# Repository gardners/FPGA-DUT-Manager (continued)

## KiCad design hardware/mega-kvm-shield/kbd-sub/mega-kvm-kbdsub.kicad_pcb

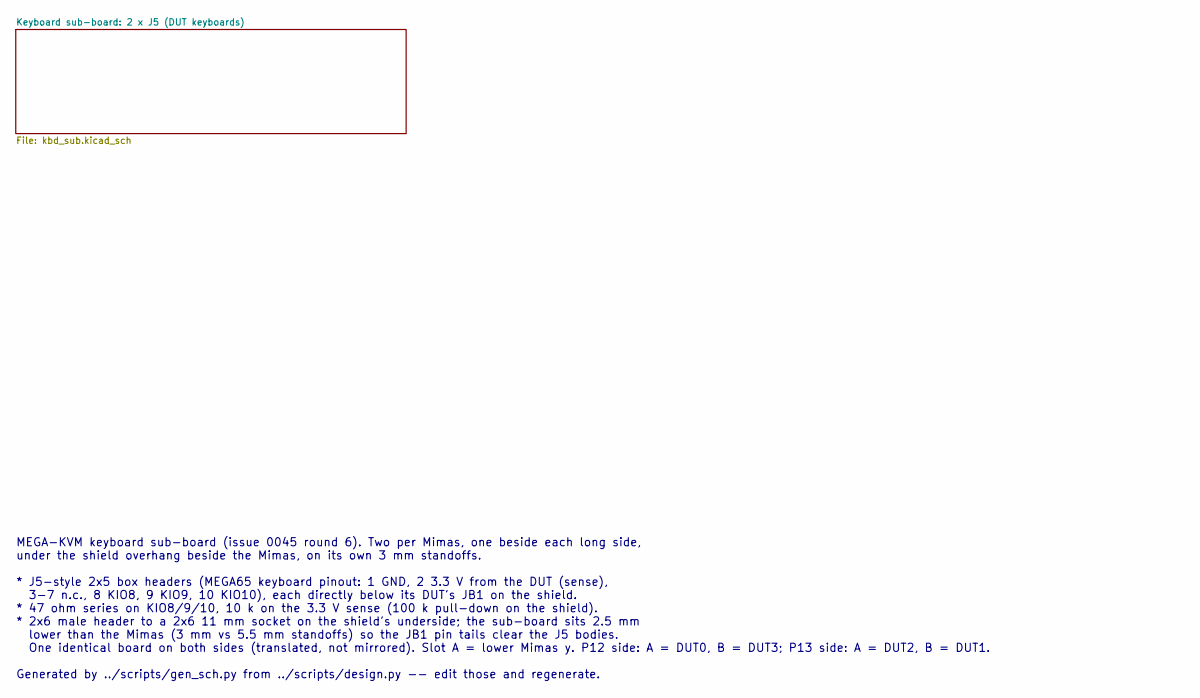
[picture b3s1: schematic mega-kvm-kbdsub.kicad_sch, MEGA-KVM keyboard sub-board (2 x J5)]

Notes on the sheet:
MEGA-KVM keyboard sub-board (issue 0045 round 6). Two per Mimas, one beside each long side, under the shield overhang beside the Mimas, on its own 3 mm standoffs. * J5-style 2x5 box headers (MEGA65 keyboard pinout: 1 GND, 2 3.3 V from the DUT (sense), 3-7 n.c., 8 KIO8, 9 KIO9, 10 KIO10), each direc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

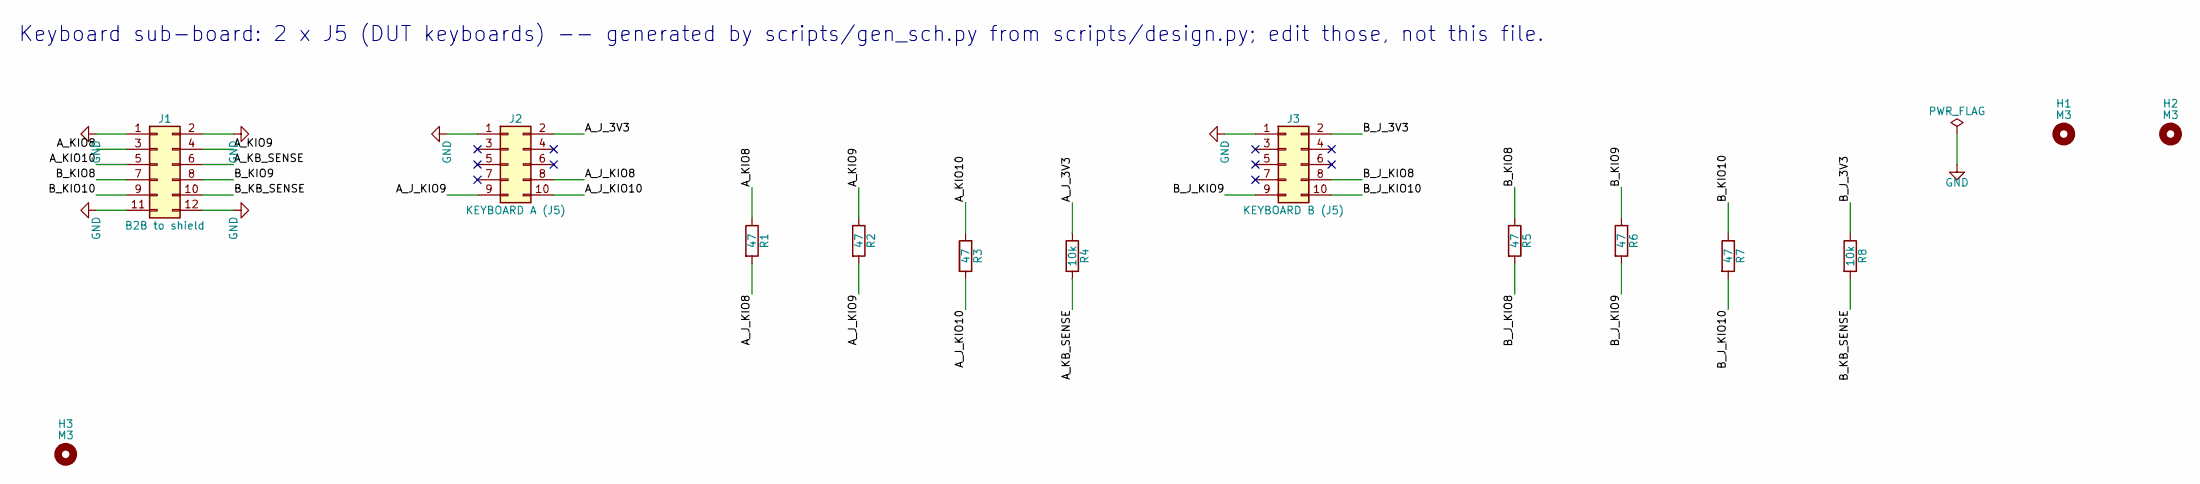
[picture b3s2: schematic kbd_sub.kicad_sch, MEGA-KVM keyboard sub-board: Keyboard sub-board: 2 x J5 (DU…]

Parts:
H1, H2, H3: M3; MountingHole_3.2mm_M3
J1: B2B to shield; PinHeader_2x06_P2.54mm_Vertical
J2: KEYBOARD A (J5); IDC-Header_2x05_P2.54mm_Horizontal
J3: KEYBOARD B (J5); IDC-Header_2x05_P2.54mm_Horizontal
R1, R2, R3, R5, R6, R7: 47; R_0402_1005Metric; LCSC C25118
R4, R8: 10k; R_0402_1005Metric; LCSC C25744

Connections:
A_J_3V3: J2.2, R4.1
A_J_KIO8: J2.8, R1.2
A_J_KIO9: J2.9, R2.2
A_J_KIO10: J2.10, R3.2
A_KB_SENSE: J1.6, R4.2
A_KIO8: J1.3, R1.1
A_KIO9: J1.4, R2.1
A_KIO10: J1.5, R3.1
B_J_3V3: J3.2, R8.1
B_J_KIO8: J3.8, R5.2
B_J_KIO9: J3.9, R6.2
B_J_KIO10: J3.10, R7.2
B_KB_SENSE: J1.10, R8.2
B_KIO8: J1.7, R5.1
B_KIO9: J1.8, R6.1
B_KIO10: J1.9, R7.1
GND: J1.1, J1.2, J1.11, J1.12, J2.1, J3.1

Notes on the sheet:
Keyboard sub-board: 2 x J5 (DUT keyboards) -- generated by scripts/gen_sch.py from scripts/design.py; edit those, not this file.

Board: 2 copper layers, 14 parts (0 on the bottom side), 17 nets, no tracks yet.

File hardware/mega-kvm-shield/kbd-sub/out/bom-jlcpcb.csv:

Comment,Designator,Footprint,LCSC Part #,MPN,Qty
B2B to shield,J1,PinHeader_2x06_P2.54mm_Vertical,TBD,,1
KEYBOARD A (J5),J2,IDC-Header_2x05_P2.54mm_Horizontal,TBD,,1
KEYBOARD B (J5),J3,IDC-Header_2x05_P2.54mm_Horizontal,TBD,,1
47,"R1,R2,R3,R5,R6,R7",R_0402_1005Metric,C25118,,6
10k,"R4,R8",R_0402_1005Metric,C25744,,2

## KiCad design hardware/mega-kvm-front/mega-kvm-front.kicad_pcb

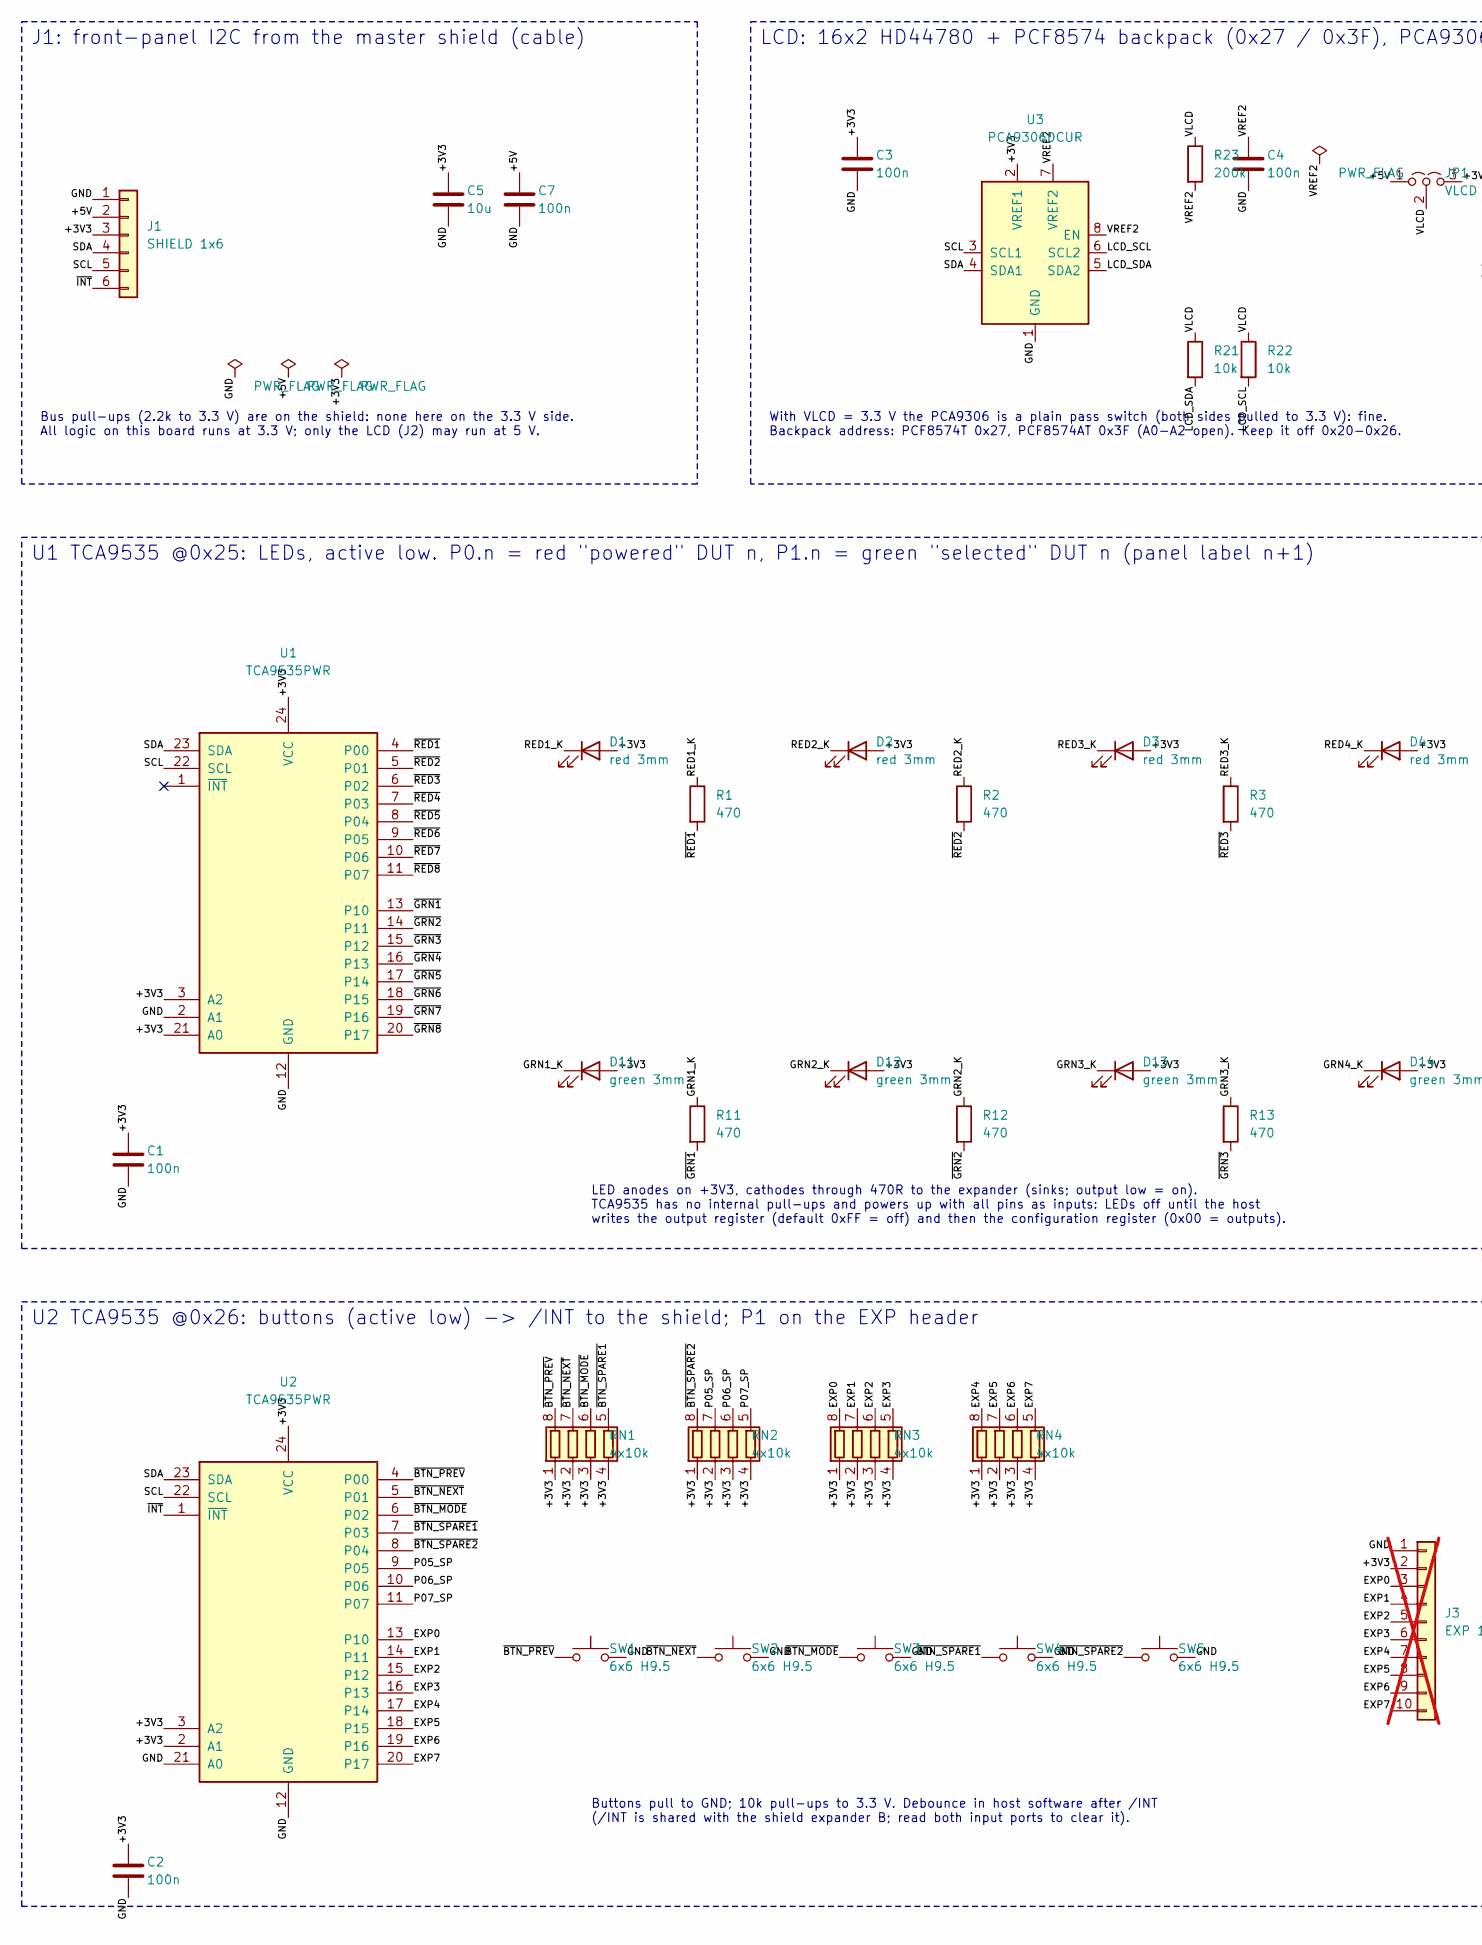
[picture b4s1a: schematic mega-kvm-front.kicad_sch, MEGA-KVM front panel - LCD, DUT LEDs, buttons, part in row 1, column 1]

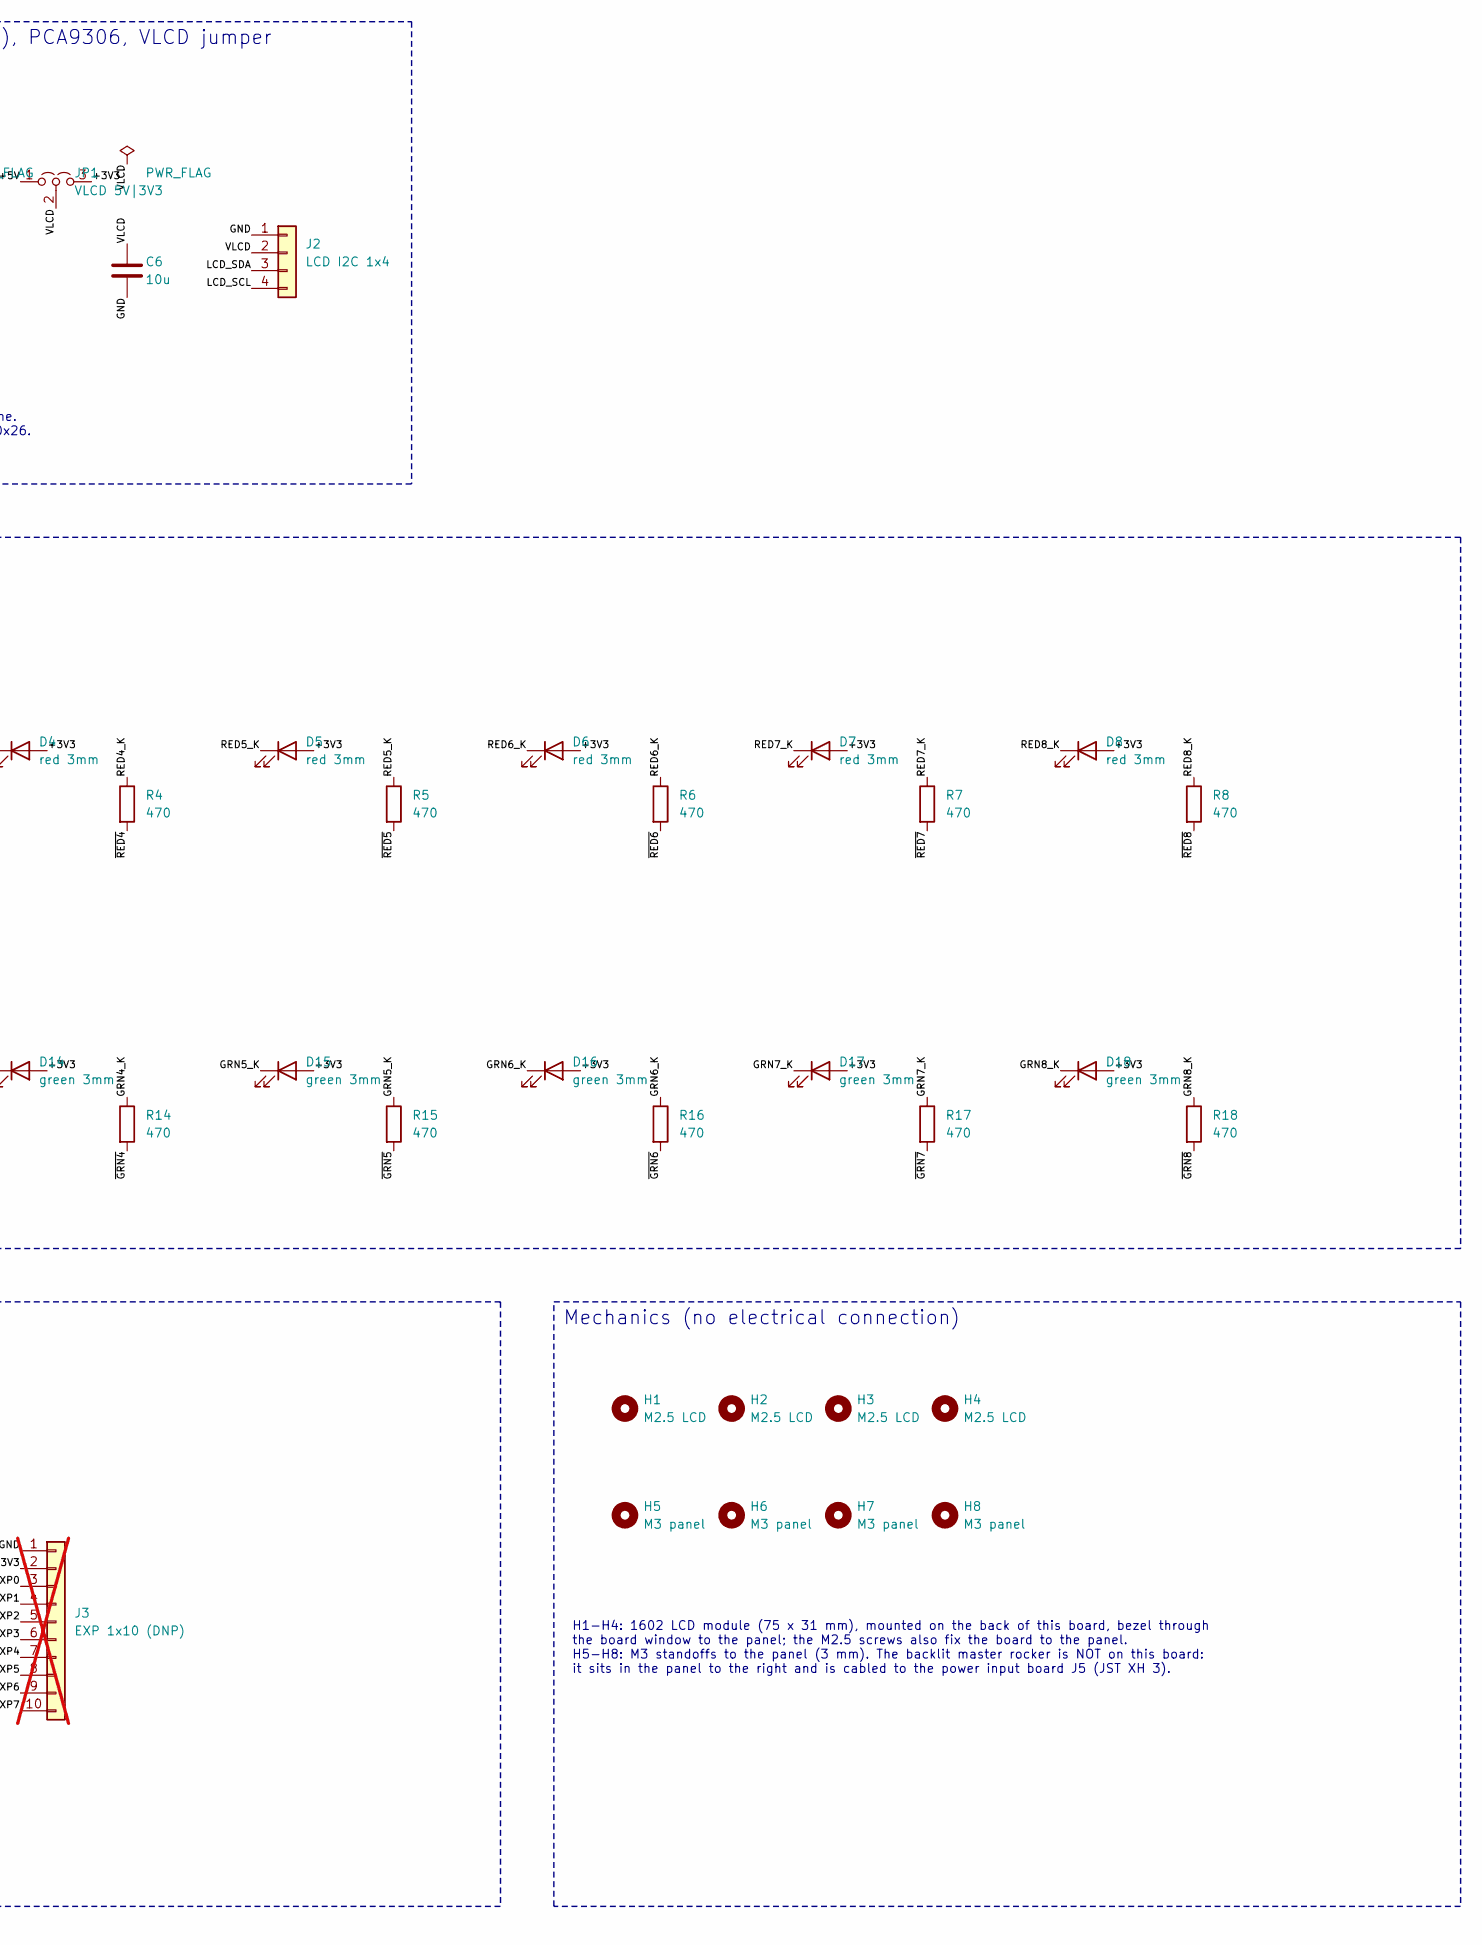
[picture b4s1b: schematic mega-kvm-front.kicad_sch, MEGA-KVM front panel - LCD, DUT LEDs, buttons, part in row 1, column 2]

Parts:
C1, C2, C3, C4, C7: 100n; C_0603_1608Metric; Voltage 50V; LCSC C14663
C5, C6: 10u; C_0603_1608Metric; Voltage 10V; LCSC C19702
D1, D2, D3, D4, D5, D6, D7, D8: red 3mm; LED_D3.0mm; MPN Everlight 204-10SDRD/S530-A3-L (3 mm re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; LCSC C84774
D11, D12, D13, D14, D15, D16, D17, D18: green 3mm; LED_D3.0mm; MPN Everlight 204-10SYGD/S530-E3 (3 mm yell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; LCSC C85161
H1, H2, H3, H4: M2.5 LCD; MountingHole_2.7mm_M2.5
H5, H6, H7, H8: M3 panel; MountingHole_3.2mm_M3
J1: SHIELD 1x6; PinHeader_1x06_P2.54mm_Vertical; LCSC C37208
J2: LCD I2C 1x4; PinHeader_1x04_P2.54mm_Vertical; LCSC C124378
J3: EXP 1x10 (DNP); PinHeader_1x10_P2.54mm_Vertical; LCSC C57369; not fitted
JP1: VLCD 5V|3V3; PinHeader_1x03_P2.54mm_Vertical; LCSC C49257
R1, R2, R3, R4, R5, R6, R7, R8, R11, R12, R13, R14, R15, R16, R17, R18: 470; R_0603_1608Metric; Tolerance 1%; LCSC C23179
R21, R22: 10k; R_0603_1608Metric; Tolerance 1%; LCSC C25804
R23: 200k; R_0603_1608Metric; Tolerance 1%; LCSC C25811
RN1, RN2, RN3, RN4: 4x10k; R_Array_Convex_4x0603; MPN UNI-ROYAL 4D03WGJ0103T5E; LCSC C29718
SW1, SW2, SW3, SW4, SW5: 6x6 H9.5; SW_PUSH_6mm_H9.5mm; MPN HRO K2-1102DP-L4SW-04 (6x6 mm THT, 9.5 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; LCSC C136679
U1, U2: TCA9535PWR; TSSOP-24_4.4x7.8mm_P0.65mm; MPN TI TCA9535PWR; LCSC C130204
U3: PCA9306DCUR; VSSOP-8_2.3x2mm_P0.5mm; MPN TI PCA9306DCUR; LCSC C33196

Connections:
/+3V3: C1.1, C2.1, C3.1, C5.1, D1.2 (A), D2.2 (A), D3.2 (A), D4.2 (A), D5.2 (A), D6.2 (A), D7.2 (A), D8.2 (A), D11.2 (A), D12.2 (A), D13.2 (A), D14.2 (A), D15.2 (A), D16.2 (A), D17.2 (A), D18.2 (A), J1.3, J3.2, JP1.3 (B), RN1.1 (R1.1), RN1.2 (R2.1), RN1.3 (R3.1), RN1.4 (R4.1), RN2.1 (R1.1), RN2.2 (R2.1), RN2.3 (R3.1), RN2.4 (R4.1), RN3.1 (R1.1), RN3.2 (R2.1), RN3.3 (R3.1), RN3.4 (R4.1), RN4.1 (R1.1), RN4.2 (R2.1), RN4.3 (R3.1), RN4.4 (R4.1), U1.3 (A2), U1.21 (A0), U1.24 (VCC), U2.2 (A1), U2.3 (A2), U2.24 (VCC), U3.2 (VREF1)
/+5V: C7.1, J1.2, JP1.1 (A)
/EXP0: J3.3, RN3.8 (R1.2), U2.13 (P10)
/EXP1: J3.4, RN3.7 (R2.2), U2.14 (P11)
/EXP2: J3.5, RN3.6 (R3.2), U2.15 (P12)
/EXP3: J3.6, RN3.5 (R4.2), U2.16 (P13)
/EXP4: J3.7, RN4.8 (R1.2), U2.17 (P14)
/EXP5: J3.8, RN4.7 (R2.2), U2.18 (P15)
/EXP6: J3.9, RN4.6 (R3.2), U2.19 (P16)
/EXP7: J3.10, RN4.5 (R4.2), U2.20 (P17)
/GND: C1.2, C2.2, C3.2, C4.2, C5.2, C6.2, C7.2, J1.1, J2.1, J3.1, SW1.2, SW2.2, SW3.2, SW4.2, SW5.2, U1.2 (A1), U1.12 (GND), U2.12 (GND), U2.21 (A0), U3.1 (GND)
/GRN1_K: D11.1 (K), R11.1
/GRN2_K: D12.1 (K), R12.1
/GRN3_K: D13.1 (K), R13.1
/GRN4_K: D14.1 (K), R14.1
/GRN5_K: D15.1 (K), R15.1
/GRN6_K: D16.1 (K), R16.1
/GRN7_K: D17.1 (K), R17.1
/GRN8_K: D18.1 (K), R18.1
/LCD_SCL: J2.4, R22.2, U3.6 (SCL2)
/LCD_SDA: J2.3, R21.2, U3.5 (SDA2)
/P05_SP: RN2.7 (R2.2), U2.9 (P05)
/P06_SP: RN2.6 (R3.2), U2.10 (P06)
/P07_SP: RN2.5 (R4.2), U2.11 (P07)
/RED1_K: D1.1 (K), R1.1
/RED2_K: D2.1 (K), R2.1
/RED3_K: D3.1 (K), R3.1
/RED4_K: D4.1 (K), R4.1
/RED5_K: D5.1 (K), R5.1
/RED6_K: D6.1 (K), R6.1
/RED7_K: D7.1 (K), R7.1
/RED8_K: D8.1 (K), R8.1
/SCL: J1.5, U1.22 (SCL), U2.22 (SCL), U3.3 (SCL1)
/SDA: J1.4, U1.23 (SDA), U2.23 (SDA), U3.4 (SDA1)
/VLCD: C6.1, J2.2, JP1.2 (C), R21.1, R22.1, R23.1
/VREF2: C4.1, R23.2, U3.7 (VREF2), U3.8 (EN)
/~BTN_MODE: RN1.6 (R3.2), SW3.1, U2.6 (P02)
/~BTN_NEXT: RN1.7 (R2.2), SW2.1, U2.5 (P01)
/~BTN_PREV: RN1.8 (R1.2), SW1.1, U2.4 (P00)
/~BTN_SPARE1: RN1.5 (R4.2), SW4.1, U2.7 (P03)
/~BTN_SPARE2: RN2.8 (R1.2), SW5.1, U2.8 (P04)
/~GRN1: R11.2, U1.13 (P10)
/~GRN2: R12.2, U1.14 (P11)
/~GRN3: R13.2, U1.15 (P12)
/~GRN4: R14.2, U1.16 (P13)
/~GRN5: R15.2, U1.17 (P14)
/~GRN6: R16.2, U1.18 (P15)
/~GRN7: R17.2, U1.19 (P16)
/~GRN8: R18.2, U1.20 (P17)
/~INT: J1.6, U2.1 (~INT)
/~RED1: R1.2, U1.4 (P00)
/~RED2: R2.2, U1.5 (P01)
/~RED3: R3.2, U1.6 (P02)
/~RED4: R4.2, U1.7 (P03)
/~RED5: R5.2, U1.8 (P04)
/~RED6: R6.2, U1.9 (P05)
/~RED7: R7.2, U1.10 (P06)
/~RED8: R8.2, U1.11 (P07)

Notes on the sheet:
J1: front-panel I2C from the master shield (cable)
Bus pull-ups (2.2k to 3.3 V) are on the shield: none here on the 3.3 V side. All logic on this board runs at 3.3 V; only the LCD (J2) may run at 5 V.
LCD: 16x2 HD44780 + PCF8574 backpack (0x27 / 0x3F), PCA9306, VLCD jumper
With VLCD = 3.3 V the PCA9306 is a plain pass switch (both sides pulled to 3.3 V): fine. Backpack address: PCF8574T 0x27, PCF8574AT 0x3F (A0-A2 open). Keep it off 0x20-0x26.
U1 TCA9535 @0x25: LEDs, active low. P0.n = red "powered" DUT n, P1.n = green "selected" DUT n (panel label n+1)
LED anodes on +3V3, cathodes through 470R to the expander (sinks; output low = on). TCA9535 has no internal pull-ups and powers up with all pins as inputs: LEDs off until the host writes the output register (default 0xFF = off) and then the configuration register (0x00 = outputs).
U2 TCA9535 @0x26: buttons (active low) -> /INT to the shield; P1 on the EXP header
Buttons pull to GND; 10k pull-ups to 3.3 V. Debounce in host software after /INT (/INT is shared with the shield expander B; read both input ports to clear it).
Mechanics (no electrical connection)
H1-H4: 1602 LCD module (75 x 31 mm), mounted on the back of this board, bezel through the board window to the panel; the M2.5 screws also fix the board to the panel. H5-H8: M3 standoffs to the panel (3 mm). The backlit master rocker is NOT on this board: it sits in the panel to the right and is cab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

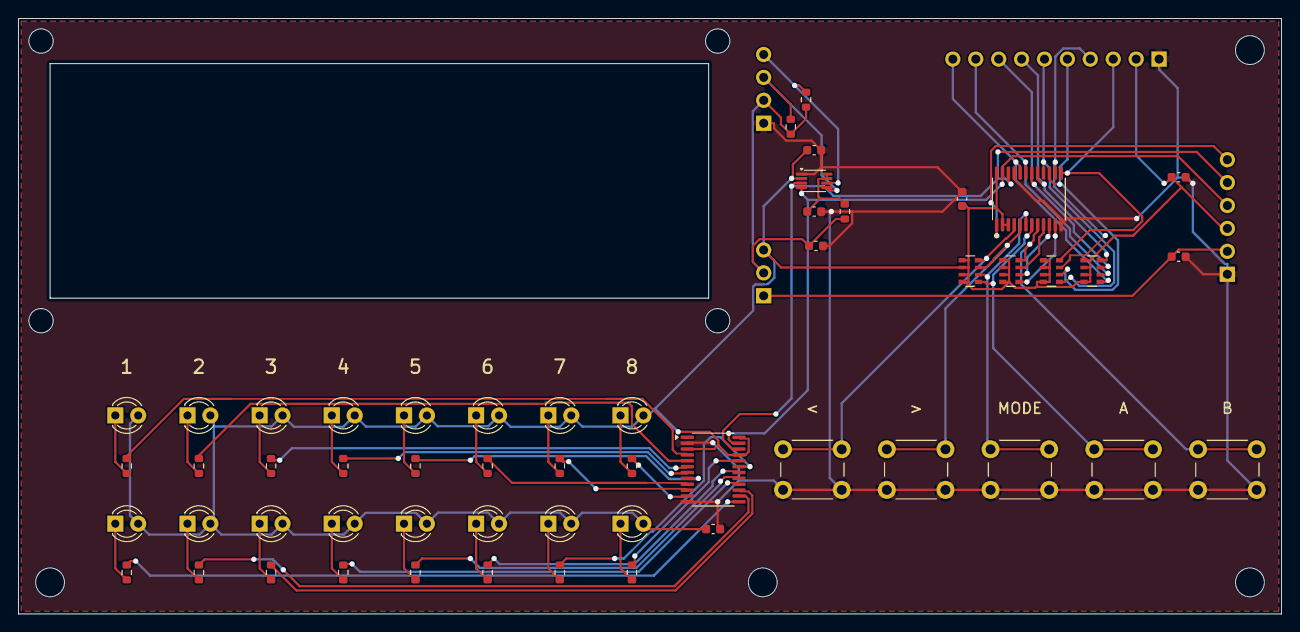
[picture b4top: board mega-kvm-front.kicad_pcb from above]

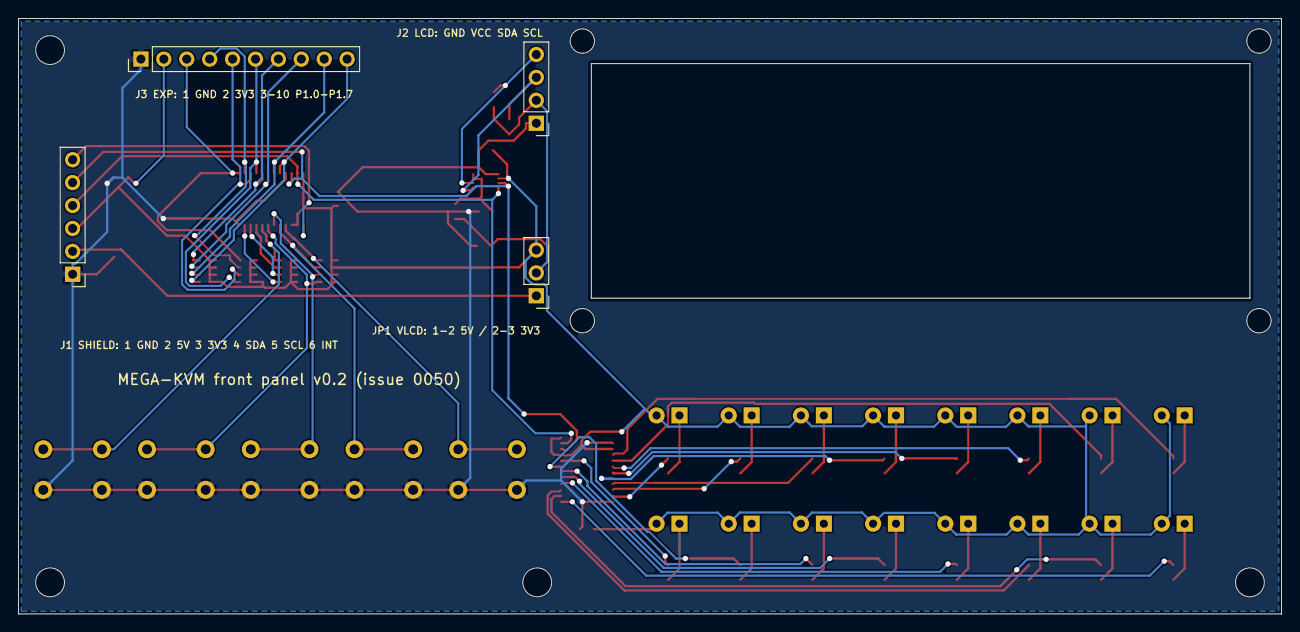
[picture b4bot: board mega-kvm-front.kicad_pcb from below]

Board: 2 copper layers, 140.0 x 66.0 mm, 66 parts (4 on the bottom side), 58 nets.

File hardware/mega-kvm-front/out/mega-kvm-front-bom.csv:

"Designator","Comment","Footprint","LCSC","MPN","JLC","Qty","DNP"
"C1,C2,C3,C4,C7","100n","Capacitor_SMD:C_0603_1608Metric","C14663","","basic","5",""
"C5,C6","10u","Capacitor_SMD:C_0603_1608Metric","C19702","","basic","2",""
"D1,D2,D3,D4,D5,D6,D7,D8","red 3mm","LED_THT:LED_D3.0mm","C84774","Everlight 204-10SDRD/S530-A3-L (3 mm red diffused, 2.0 V)","extended (THT)","8",""
"D11,D12,D13,D14,D15,D16,D17,D18","green 3mm","LED_THT:LED_D3.0mm","C85161","Everlight 204-10SYGD/S530-E3 (3 mm yellow-green diffused, 2.0 V)","extended (THT)","8",""
"J1","SHIELD 1x6","Connector_PinHeader_2.54mm:PinHeader_1x06_P2.54mm_Vertical","C37208","","extended (THT)","1",""
"J2","LCD I2C 1x4","Connector_PinHeader_2.54mm:PinHeader_1x04_P2.54mm_Vertical","C124378","","extended (THT)","1",""
"J3","EXP 1x10 (DNP)","Connector_PinHeader_2.54mm:PinHeader_1x10_P2.54mm_Vertical","C57369","","extended (THT)","1","DNP"
"JP1","VLCD 5V|3V3","Connector_PinHeader_2.54mm:PinHeader_1x03_P2.54mm_Vertical","C49257","","extended (THT)","1",""
"R1,R2,R3,R4,R5,R6,R7,R8,R11,R12,R13,R14,R15,R16,R17,R18","470","Resistor_SMD:R_0603_1608Metric","C23179","","basic","16",""
"R21,R22","10k","Resistor_SMD:R_0603_1608Metric","C25804","","basic","2",""
"R23","200k","Resistor_SMD:R_0603_1608Metric","C25811","","basic","1",""
"RN1,RN2,RN3,RN4","4x10k","Resistor_SMD:R_Array_Convex_4x0603","C29718","UNI-ROYAL 4D03WGJ0103T5E","basic","4",""
"SW1,SW2,SW3,SW4,SW5","6x6 H9.5","Button_Switch_THT:SW_PUSH_6mm_H9.5mm","C136679","HRO K2-1102DP-L4SW-04 (6x6 mm THT, 9.5 mm, round stem)","extended (THT)","5",""
"U1,U2","TCA9535PWR","Package_SO:TSSOP-24_4.4x7.8mm_P0.65mm","C130204","TI TCA9535PWR","extended","2",""
"U3","PCA9306DCUR","Package_SO:VSSOP-8_2.3x2mm_P0.5mm","C33196","TI PCA9306DCUR","extended","1",""
